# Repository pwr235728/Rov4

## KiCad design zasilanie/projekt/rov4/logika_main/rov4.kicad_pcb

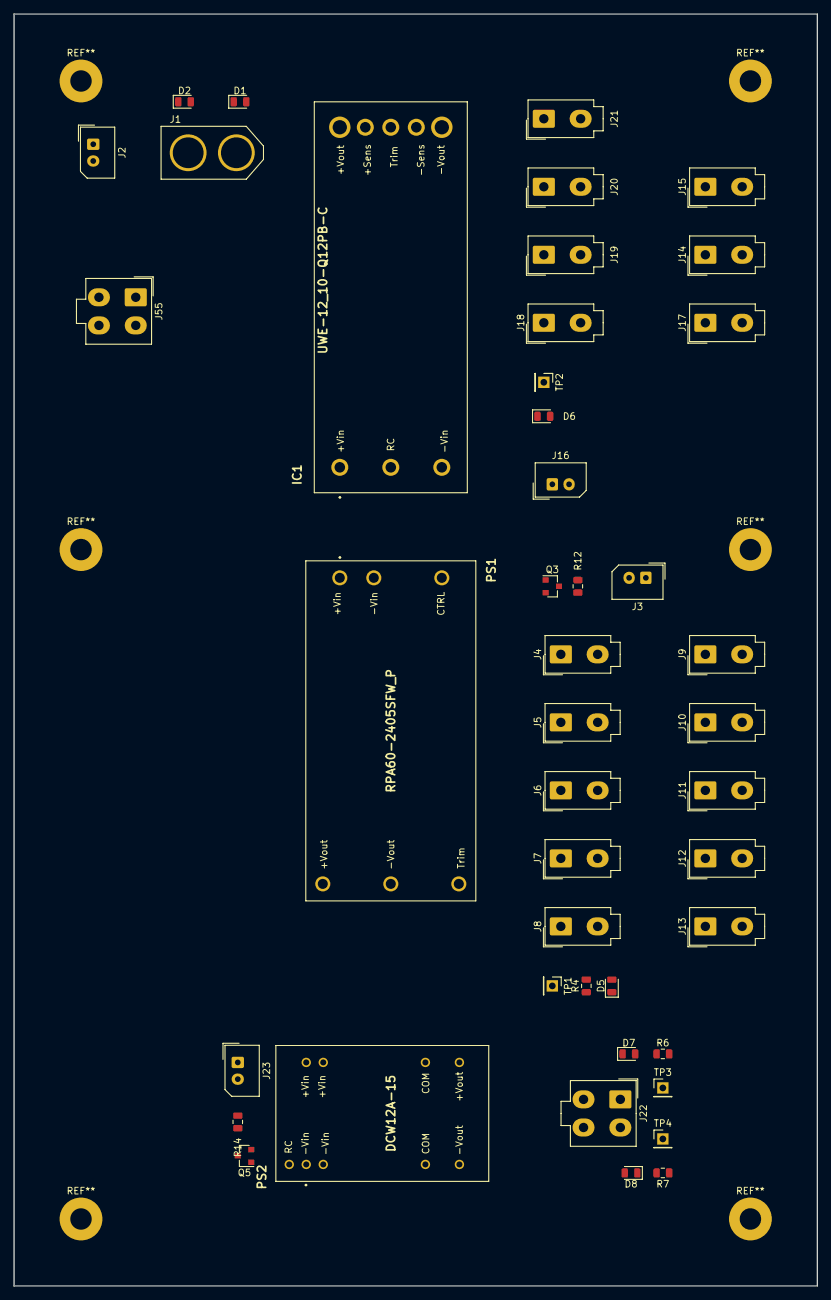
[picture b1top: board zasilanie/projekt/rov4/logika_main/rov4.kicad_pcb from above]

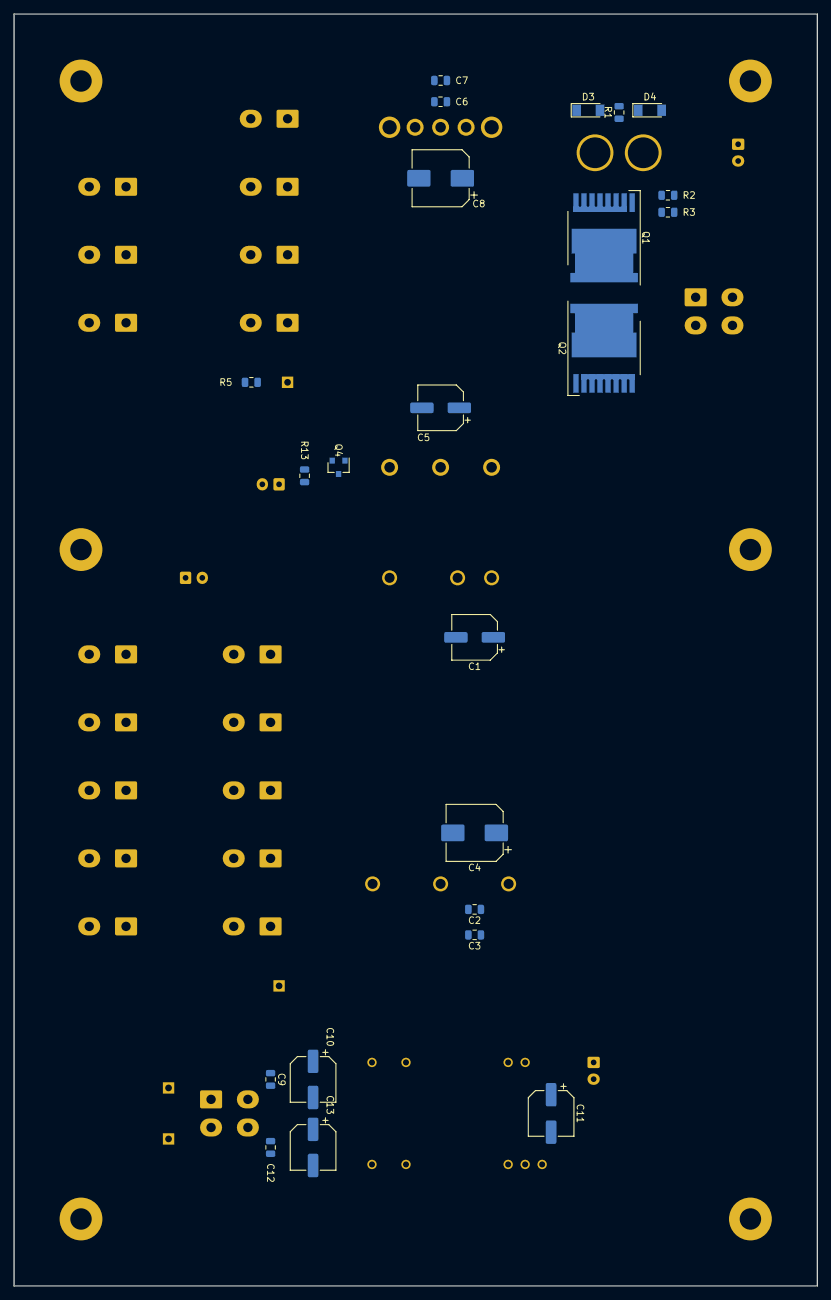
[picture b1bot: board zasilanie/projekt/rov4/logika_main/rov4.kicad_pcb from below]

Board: 2 copper layers, 120.0 x 190.0 mm, 67 parts (23 on the bottom side), 27 nets, no tracks yet.

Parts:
C1, C5, C11: 33uF; CP_Elec_6.3x5.4
C2, C6, C9, C12: 100nF; C_0805_2012Metric
C3, C7: 10uF; C_0805_2012Metric
C4, C8: 200uF; CP_Elec_8x10
C10, C13: 100uF; CP_Elec_6.3x7.7
D1: LED_G; LED_0805_2012Metric
D2: LED_R; LED_0805_2012Metric
D3, D4: BAT48; D_MiniMELF
D5, D6, D7, D8: LED_B; LED_0805_2012Metric
IC1: UWE-12_10-Q12PB-C; UWE-12_10-Q12P-C
J1: Battery digital; XT60UPB-M
J2: Reed switch; Molex_SPOX_5267-02A_1x02_P2.50mm_Vertical
J3: RC_D_5V; Molex_SPOX_5267-02A_1x02_P2.50mm_Vertical
J4: Manip_SterSil2; Molex_Mini-Fit_Jr_5566-02A_2x01_P4.20mm_Vertical
J5: Manip_SterSil1; Molex_Mini-Fit_Jr_5566-02A_2x01_P4.20mm_Vertical
J6, J7, J20, J21: Extra; Molex_Mini-Fit_Jr_5566-02A_2x01_P4.20mm_Vertical
J8: STM32; Molex_Mini-Fit_Jr_5566-02A_2x01_P4.20mm_Vertical
J9: RPi; Molex_Mini-Fit_Jr_5566-02A_2x01_P4.20mm_Vertical
J10: Router; Molex_Mini-Fit_Jr_5566-02A_2x01_P4.20mm_Vertical
J11: Switch; Molex_Mini-Fit_Jr_5566-02A_2x01_P4.20mm_Vertical
J12: Enko_inkrementalny; Molex_Mini-Fit_Jr_5566-02A_2x01_P4.20mm_Vertical
J13: Torpedy, hall, laser; Molex_Mini-Fit_Jr_5566-02A_2x01_P4.20mm_Vertical
J14: Enko_absolutny_1; Molex_Mini-Fit_Jr_5566-02A_2x01_P4.20mm_Vertical
J15: Enko_absolutny_2; Molex_Mini-Fit_Jr_5566-02A_2x01_P4.20mm_Vertical
J16: RC_D_12V; Molex_SPOX_5267-02A_1x02_P2.50mm_Vertical
J17: Xavier; Molex_Mini-Fit_Jr_5566-02A_2x01_P4.20mm_Vertical
J18: Kamera 1; Molex_Mini-Fit_Jr_5566-02A_2x01_P4.20mm_Vertical
J19: Kamera 2; Molex_Mini-Fit_Jr_5566-02A_2x01_P4.20mm_Vertical
J22: hydrofony; Molex_Mini-Fit_Jr_5566-04A_2x02_P4.20mm_Vertical
J23: RC_D_15V; Molex_SPOX_5267-02A_1x02_P2.50mm_Vertical
J55: LP_OUT; Molex_Mini-Fit_Jr_5566-04A_2x02_P4.20mm_Vertical
PS1: RPA60-2405SFW_P
PS2: DCW12A-15
Q1, Q2: IPT004N03L; Infineon_PG-HSOF-8-1
Q3, Q4, Q5: BC847A; SOT-23
R1: 3k; R_0805_2012Metric
R2: 100; R_0805_2012Metric
R3: 10k; R_0805_2012Metric
R4: 400; R_0805_2012Metric
R5: 1k8; R_0805_2012Metric
R6, R7: 2k4; R_0805_2012Metric
R12, R13, R14: 3k3; R_0805_2012Metric
TP1, TP3: D_5V; PinHeader_1x01_P2.54mm_Vertical
TP2: D_12V; PinHeader_1x01_P2.54mm_Vertical
TP4: D_-5V; PinHeader_1x01_P2.54mm_Vertical

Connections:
+BattDigit: C1.1, C5.1, C11.1, IC1.1, J1.1, J2.2, J55.1, J55.2, PS1.1, PS2.22, PS2.23, Q2.1, R1.1
-BattDigit: C1.2, C2.2, C3.2, C4.2, C5.2, C6.2, C7.2, C8.2, C9.2, C10.2, C11.2, C12.1, C13.1, D6.1, D7.1, D8.2, IC1.3, IC1.4, IC1.5, J4.2, J6.2, J7.2, J8.2, J9.2, J11.2, J12.2, J13.2, J14.2, J15.2, J17.2, J18.2, J19.2, J20.2, J21.2, J22.3, J22.4, J55.3, J55.4, PS1.2, PS1.5, PS2.2, PS2.3, PS2.9, PS2.16, Q2.2, Q3.2, Q4.2, Q5.2, R4.2
/logika_main/-Batt: D1.1, D2.2, J1.2, Q1.2, R3.2
unnamed: C2.1, C3.1, C4.1, D5.2, J4.1, J5.1, J6.1, J7.1, J8.1, J9.1, J10.1, J11.1, J12.1, J13.1, PS1.6, TP1.1
unnamed: C6.1, C7.1, C8.1, IC1.7, IC1.8, J14.1, J15.1, J17.1, J18.1, J19.1, J20.1, J21.1, R5.2, TP2.1
unnamed: C9.1, C10.1, J22.1, PS2.14, R6.2, TP3.1
unnamed: C12.2, C13.2, J22.2, PS2.11, R7.1, TP4.1
unnamed: D1.2, D3.1
unnamed: D2.1, D4.2
unnamed: D3.2, D4.1, R1.2
unnamed: D5.1, R4.1
unnamed: D6.2, R5.1
unnamed: D7.2, R6.1
unnamed: D8.1, R7.2
unnamed: IC1.2, Q4.3
unnamed: J2.1, R2.1
unnamed: J3.1, R12.2
unnamed: J5.2, J10.2
unnamed: J16.1, R13.2
unnamed: J23.1, R14.2
unnamed: PS1.3, Q3.3
unnamed: PS2.1, Q5.3
unnamed: Q1.1, R2.2, R3.1
unnamed: Q1.3, Q2.3
unnamed: Q3.1, R12.1
unnamed: Q4.1, R13.1
unnamed: Q5.1, R14.1

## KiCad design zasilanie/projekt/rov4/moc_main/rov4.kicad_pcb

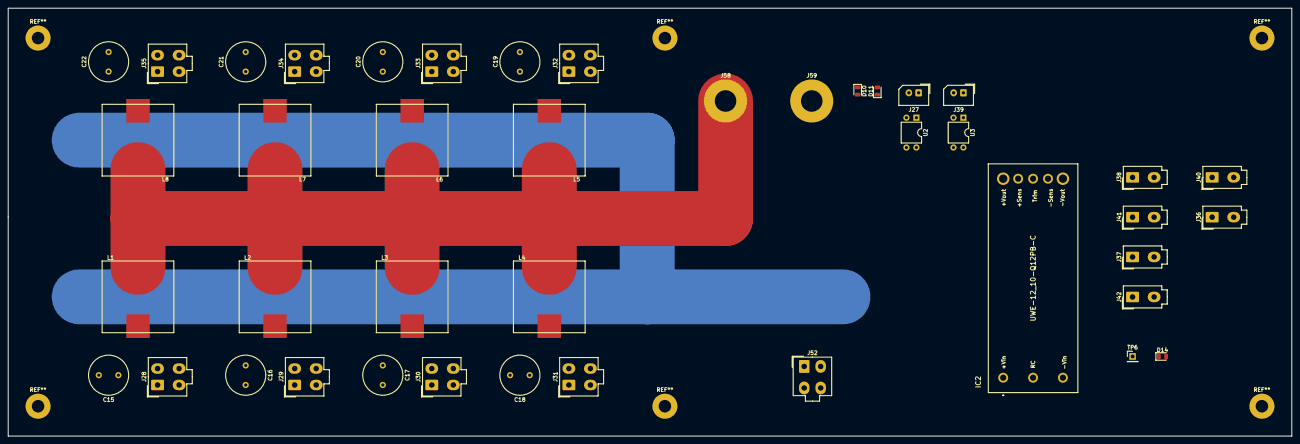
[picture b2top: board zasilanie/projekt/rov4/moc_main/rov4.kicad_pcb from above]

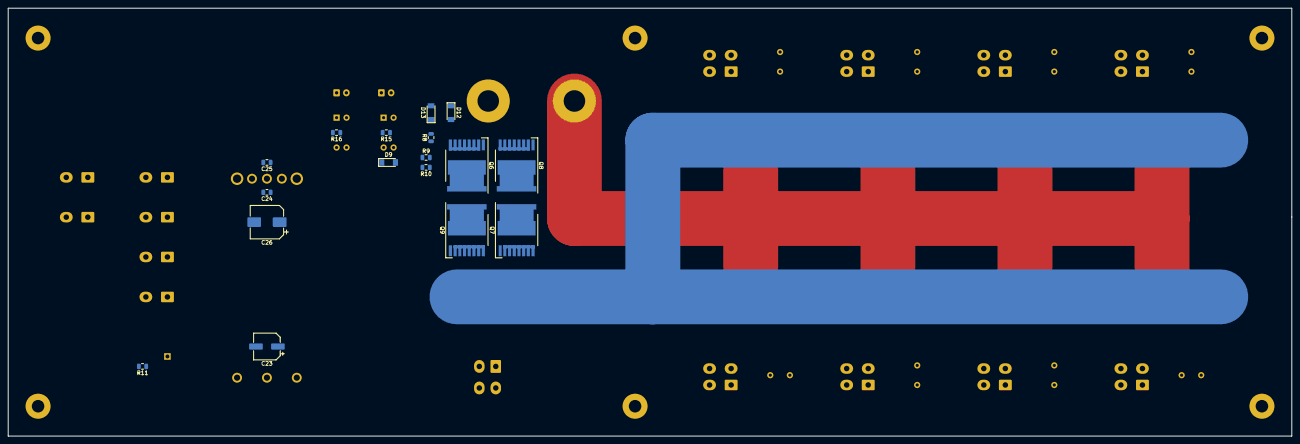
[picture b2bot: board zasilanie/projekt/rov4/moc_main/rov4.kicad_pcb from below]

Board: 2 copper layers, 327.7 x 109.2 mm, 59 parts (17 on the bottom side), 26 nets.

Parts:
C15, C16, C17, C18, C19, C20, C21, C22: C; C_Radial_D10.0mm_H20.0mm_P5.00mm
C23: 33uF; CP_Elec_6.3x5.4
C24: 100nF; C_0805_2012Metric
C25: 10uF; C_0805_2012Metric
C26: 200uF; CP_Elec_8x10
D9, D12, D13: BAT48; D_MiniMELF
D10: LED_G; LED_0805_2012Metric
D11: LED_R; LED_0805_2012Metric
D14: LED_B; LED_0805_2012Metric
IC2: UWE-12_10-Q12PB-C; UWE-12_10-Q12P-C
J27: HP_Enable; Molex_SPOX_5267-02A_1x02_P2.50mm_Vertical
J28: ESC1; Molex_Mini-Fit_Jr_5566-04A_2x02_P4.20mm_Vertical
J29: ESC2; Molex_Mini-Fit_Jr_5566-04A_2x02_P4.20mm_Vertical
J30: ESC3; Molex_Mini-Fit_Jr_5566-04A_2x02_P4.20mm_Vertical
J31: ESC4; Molex_Mini-Fit_Jr_5566-04A_2x02_P4.20mm_Vertical
J32: ESC5; Molex_Mini-Fit_Jr_5566-04A_2x02_P4.20mm_Vertical
J33: ESC6; Molex_Mini-Fit_Jr_5566-04A_2x02_P4.20mm_Vertical
J34: ESC7; Molex_Mini-Fit_Jr_5566-04A_2x02_P4.20mm_Vertical
J35: ESC8; Molex_Mini-Fit_Jr_5566-04A_2x02_P4.20mm_Vertical
J36: Manip_sil_12v; Molex_Mini-Fit_Jr_5566-02A_2x01_P4.20mm_Vertical
J37: Torp_EleMagnes; Molex_Mini-Fit_Jr_5566-02A_2x01_P4.20mm_Vertical
J38, J40: Extra; Molex_Mini-Fit_Jr_5566-02A_2x01_P4.20mm_Vertical
J39: RC_HP_12V; Molex_SPOX_5267-02A_1x02_P2.50mm_Vertical
J41: Manip_Silnik_1; Molex_Mini-Fit_Jr_5566-02A_2x01_P4.20mm_Vertical
J42: Manip_Silnik_2; Molex_Mini-Fit_Jr_5566-02A_2x01_P4.20mm_Vertical
J52: HP_OUT; Molex_Mini-Fit_Jr_5566-04A_2x02_P4.20mm_Vertical
J58: +BattPower; MountingHole_5.5mm_Pad
J59: -BattPower; MountingHole_5.5mm_Pad
L1, L2, L3, L4, L5, L6, L7, L8: L; 74435571100
Q6, Q7, Q8, Q9: IPT004N03L; Infineon_PG-HSOF-8-1
R8: 3k; R_0805_2012Metric
R9: 100; R_0805_2012Metric
R10: 10k; R_0805_2012Metric
R11: 1k8; R_0805_2012Metric
R15, R16: 680; R_0805_2012Metric
TP6: HP_12V; PinHeader_1x01_P2.54mm_Vertical
U2, U3: Transoptor; DIP-4_W7.62mm

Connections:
+BattPow: C23.1, D9.1, IC2.1, J52.1, J52.2, J58.1, L1.1, L2.1, L3.1, L4.1, L5.1, L6.1, L7.1, L8.1, Q7.1, Q9.1, R8.1, U2.4
-BattPow: C15.2, C16.2, C17.2, C18.2, C19.2, C20.2, C21.2, C22.2, C23.2, C24.2, C25.2, C26.2, D14.1, IC2.3, IC2.4, IC2.5, J28.3, J28.4, J29.3, J29.4, J30.3, J30.4, J31.3, J31.4, J32.3, J32.4, J33.3, J33.4, J34.3, J34.4, J35.3, J35.4, J36.2, J37.2, J38.2, J40.2, J41.2, J42.2, J52.3, J52.4, Q7.2, Q9.2, U3.3
unnamed: C15.1, J28.1, J28.2, L1.2
unnamed: C16.1, J29.1, J29.2, L2.2
unnamed: C17.1, J30.1, J30.2, L3.2
unnamed: C18.1, J31.1, J31.2, L4.2
unnamed: C19.1, J32.1, J32.2, L5.2
unnamed: C20.1, J33.1, J33.2, L6.2
unnamed: C21.1, J34.1, J34.2, L7.2
unnamed: C22.1, J35.1, J35.2, L8.2
unnamed: C24.1, C25.1, C26.1, IC2.7, IC2.8, J36.1, J37.1, J38.1, J40.1, J41.1, J42.1, R11.1, TP6.1
unnamed: D9.2, R9.1, U2.3
unnamed: D10.1, D11.2, J59.1, Q6.2, Q8.2, R10.2
unnamed: D10.2, D12.1
unnamed: D11.1, D13.2
unnamed: D12.2, D13.1, R8.2
unnamed: D14.2, R11.2
unnamed: IC2.2, U3.4
unnamed: J27.1, R15.2
unnamed: J27.2, U2.2
unnamed: J39.1, R16.2
unnamed: J39.2, U3.2
unnamed: Q6.1, Q8.1, R9.2, R10.1
unnamed: Q6.3, Q7.3, Q8.3, Q9.3
unnamed: R15.1, U2.1
unnamed: R16.1, U3.1
